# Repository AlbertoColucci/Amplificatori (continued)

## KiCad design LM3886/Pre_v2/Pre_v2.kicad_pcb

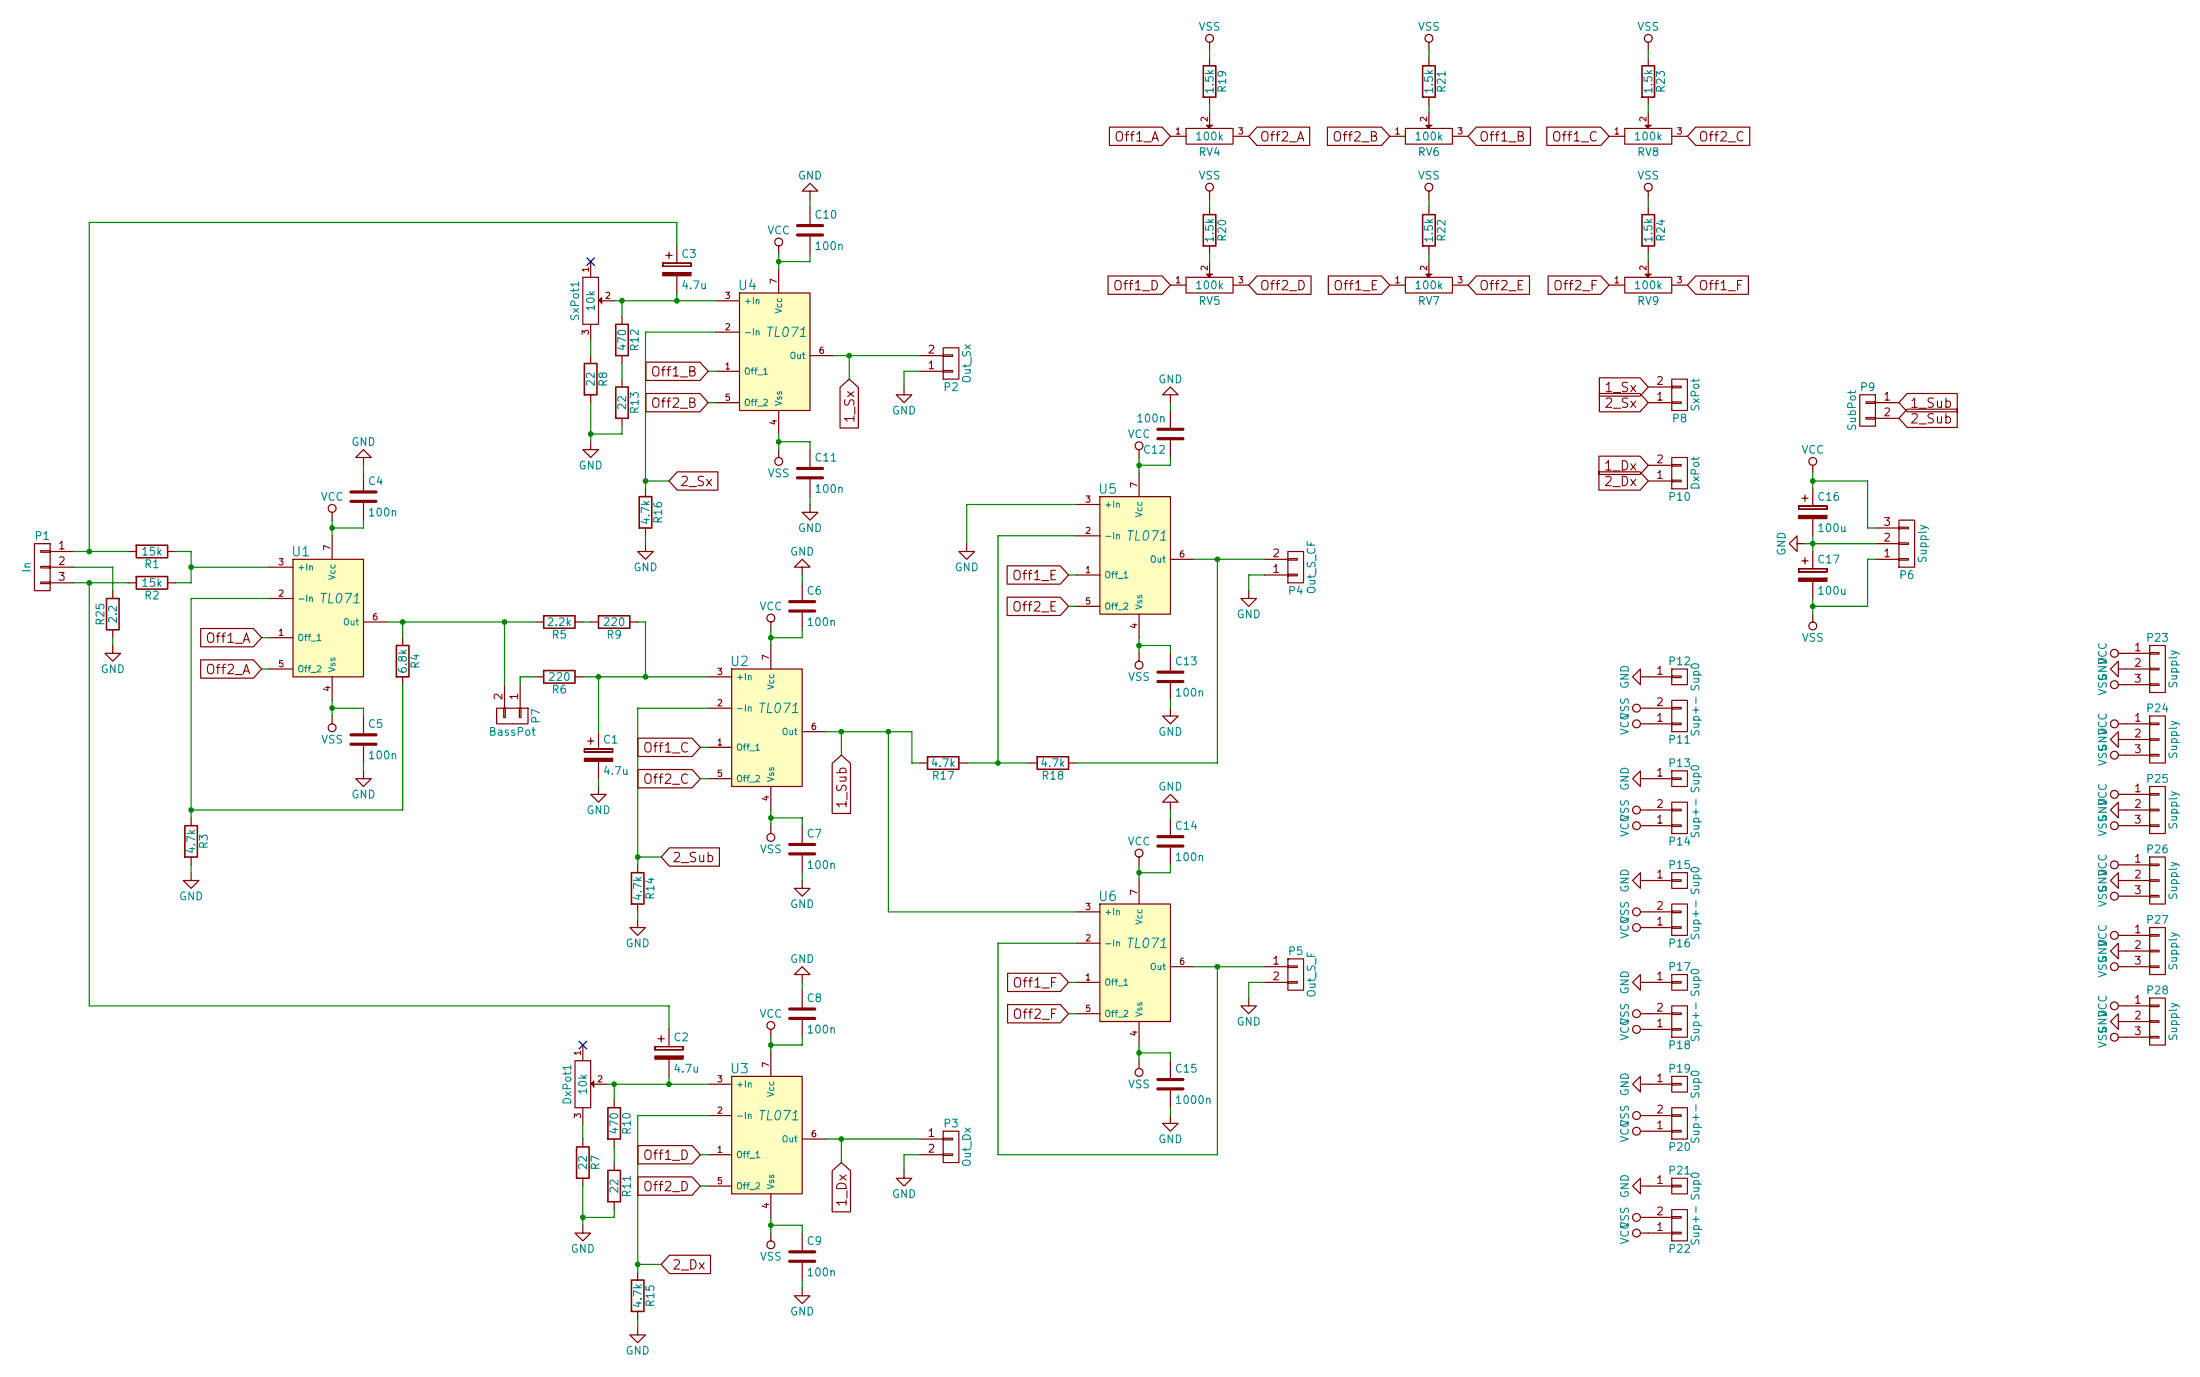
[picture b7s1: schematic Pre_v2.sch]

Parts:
C1, C2, C3: 4.7u; Cap_5x11
C4, C5, C6, C7, C8, C9, C10, C11, C12, C13, C14: 100n; Cap_7x2.5
C15: 1000n; Cap_7x2.5
C16, C17: 100u; Cap_10_5.08
DxPot1: 10k; Potentiometer_Trimmer_Bourns_3296W
P1: In; AK300-3
P2: Out_Sx; AK300-2
P3: Out_Dx; AK300-2
P4: Out_S_CF; AK300-2
P5: Out_S_F; AK300-2
P6: Supply; AK300-3
P7: BassPot; 2-Pin
P8: SxPot; 2-Pin
P9: SubPot; 2-Pin
P10: DxPot; 2-Pin
P11, P14, P16, P18, P20, P22: Sup+-; 2-Pin
P12, P13, P15, P17, P19, P21: Sup0; 1pin
P23, P24, P25, P26, P27, P28: Supply; 3-Pin
R1, R2: 15k; Res_Orizz_10mm
R3, R14, R15, R16, R17, R18: 4.7k; Res_Orizz_10mm
R4: 6.8k; Res_Orizz_10mm
R5: 2.2k; Res_Orizz_10mm
R6, R9: 220; Res_Orizz_10mm
R7, R8, R11, R13: 22; Res_Orizz_10mm
R10, R12: 470; Res_Orizz_10mm
R19, R20, R21, R22, R23, R24: 1.5k; Res_Orizz_10mm
R25: 2.2; Res_Orizz_10mm
RV4, RV5, RV6, RV7, RV8, RV9: 100k; Potentiometer_Trimmer_ACP_CA14v_Horizontal_Px15.0mm_Py10.0mm
SxPot1: 10k; Potentiometer_Trimmer_Bourns_3296W
U1, U2, U3, U4, U5, U6: TL071; DIP-8

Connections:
1_Dx: P3.1, P10.2, U3.6 (Out)
1_Sub: P9.1, R17.2, U2.6 (Out), U6.3 (+In)
1_Sx: P2.2, P8.2, U4.6 (Out)
2_Dx: P10.1, R15.1, U3.2 (-In)
2_Sub: P9.2, R14.1, U2.2 (-In)
2_Sx: P8.1, R16.1, U4.2 (-In)
GND: C1.2, C4.1, C5.2, C6.1, C7.2, C8.1, C9.2, C10.1, C11.2, C12.2, C13.2, C14.1, C15.2, C16.2, C17.1, P2.1, P3.2, P4.1, P5.2, P6.2, P12.1, P13.1, P15.1, P17.1, P19.1, P21.1, P23.2, P24.2, P25.2, P26.2, P27.2, P28.2, R3.2, R7.2, R8.2, R11.2, R13.2, R14.2, R15.2, R16.2, R25.1, U5.3 (+In)
unnamed: C1.1, R6.1, R9.1, U2.3 (+In)
unnamed: C2.1, P1.3, R2.2
unnamed: C2.2, DxPot1.2, R10.1, U3.3 (+In)
unnamed: C3.1, P1.1, R1.2
unnamed: C3.2, R12.1, SxPot1.2, U4.3 (+In)
unnamed: DxPot1.3, R7.1
unnamed: P1.2, R25.2
unnamed: P4.2, R18.1, U5.6 (Out)
unnamed: P5.1, U6.2 (-In), U6.6 (Out)
unnamed: P7.1, R6.2
unnamed: P7.2, R4.1, R5.2, U1.6 (Out)
unnamed: R1.1, R2.1, U1.3 (+In)
unnamed: R3.1, R4.2, U1.2 (-In)
unnamed: R5.1, R9.2
unnamed: R8.1, SxPot1.3
unnamed: R10.2, R11.1
unnamed: R12.2, R13.1
unnamed: R17.1, R18.2, U5.2 (-In)
unnamed: R19.2, RV4.2
unnamed: R20.2, RV5.2
unnamed: R21.2, RV6.2
unnamed: R22.2, RV7.2
unnamed: R23.2, RV8.2
unnamed: R24.2, RV9.2
Off1_A: RV4.1, U1.1 (Off_1)
Off1_B: RV6.3, U4.1 (Off_1)
Off1_C: RV8.1, U2.1 (Off_1)
Off1_D: RV5.1, U3.1 (Off_1)
Off1_E: RV7.1, U5.1 (Off_1)
Off1_F: RV9.3, U6.1 (Off_1)
Off2_A: RV4.3, U1.5 (Off_2)
Off2_B: RV6.1, U4.5 (Off_2)
Off2_C: RV8.3, U2.5 (Off_2)
Off2_D: RV5.3, U3.5 (Off_2)
Off2_E: RV7.3, U5.5 (Off_2)
Off2_F: RV9.1, U6.5 (Off_2)
VCC: C4.2, C6.2, C8.2, C10.2, C12.1, C14.2, C16.1, P6.3, P11.1, P14.1, P16.1, P18.1, P20.1, P22.1, P23.1, P24.1, P25.1, P26.1, P27.1, P28.1, U1.7 (Vcc), U2.7 (Vcc), U3.7 (Vcc), U4.7 (Vcc), U5.7 (Vcc), U6.7 (Vcc)
VSS: C5.1, C7.1, C9.1, C11.1, C13.1, C15.1, C17.2, P6.1, P11.2, P14.2, P16.2, P18.2, P20.2, P22.2, P23.3, P24.3, P25.3, P26.3, P27.3, P28.3, R19.1, R20.1, R21.1, R22.1, R23.1, R24.1, U1.4 (Vss), U2.4 (Vss), U3.4 (Vss), U4.4 (Vss), U5.4 (Vss), U6.4 (Vss)

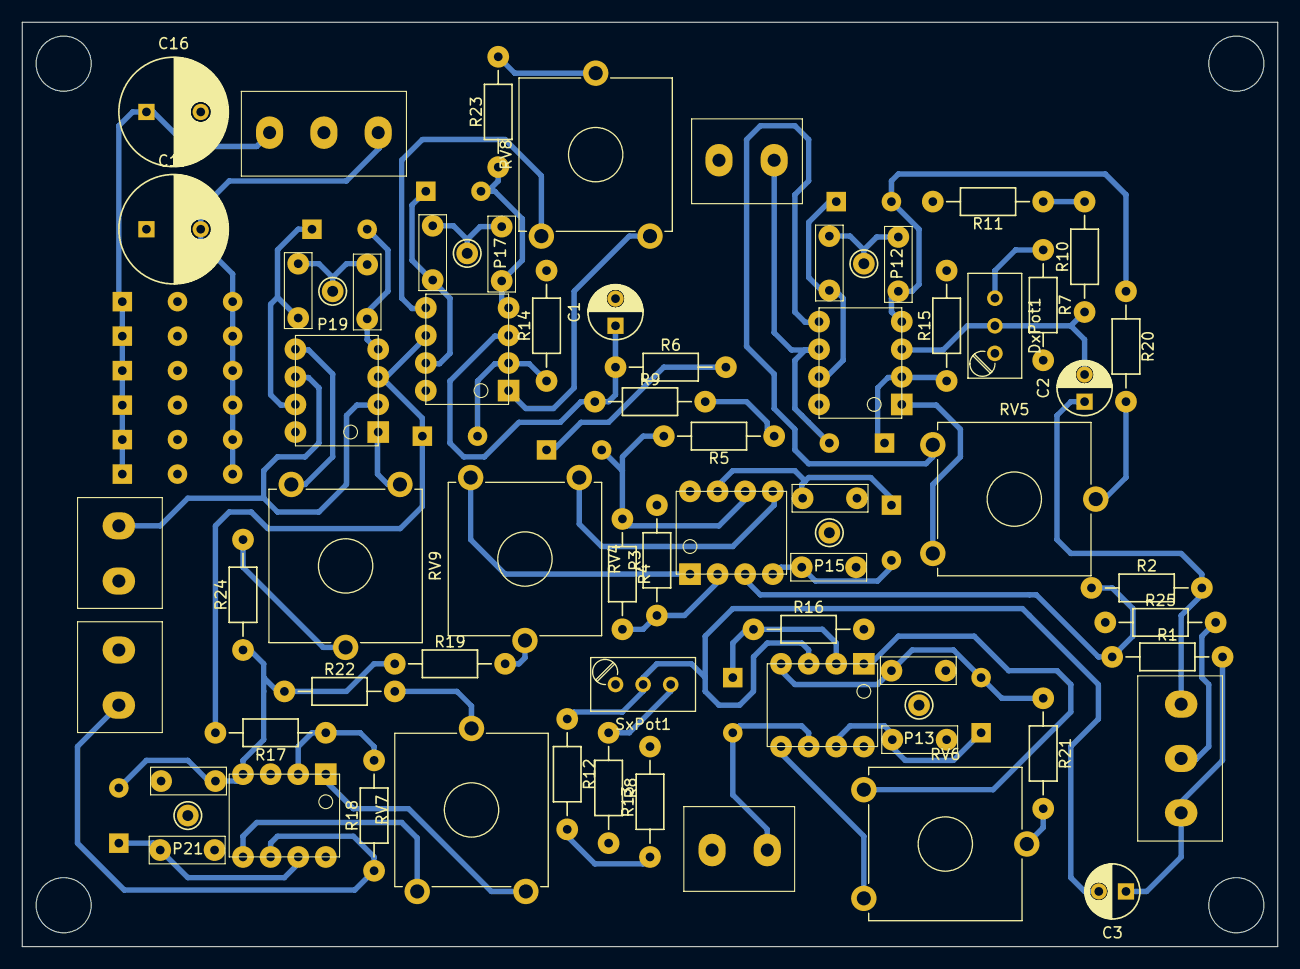
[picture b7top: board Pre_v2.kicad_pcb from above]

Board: 2 copper layers, 115.6 x 85.1 mm, 84 parts (0 on the bottom side), 45 nets.

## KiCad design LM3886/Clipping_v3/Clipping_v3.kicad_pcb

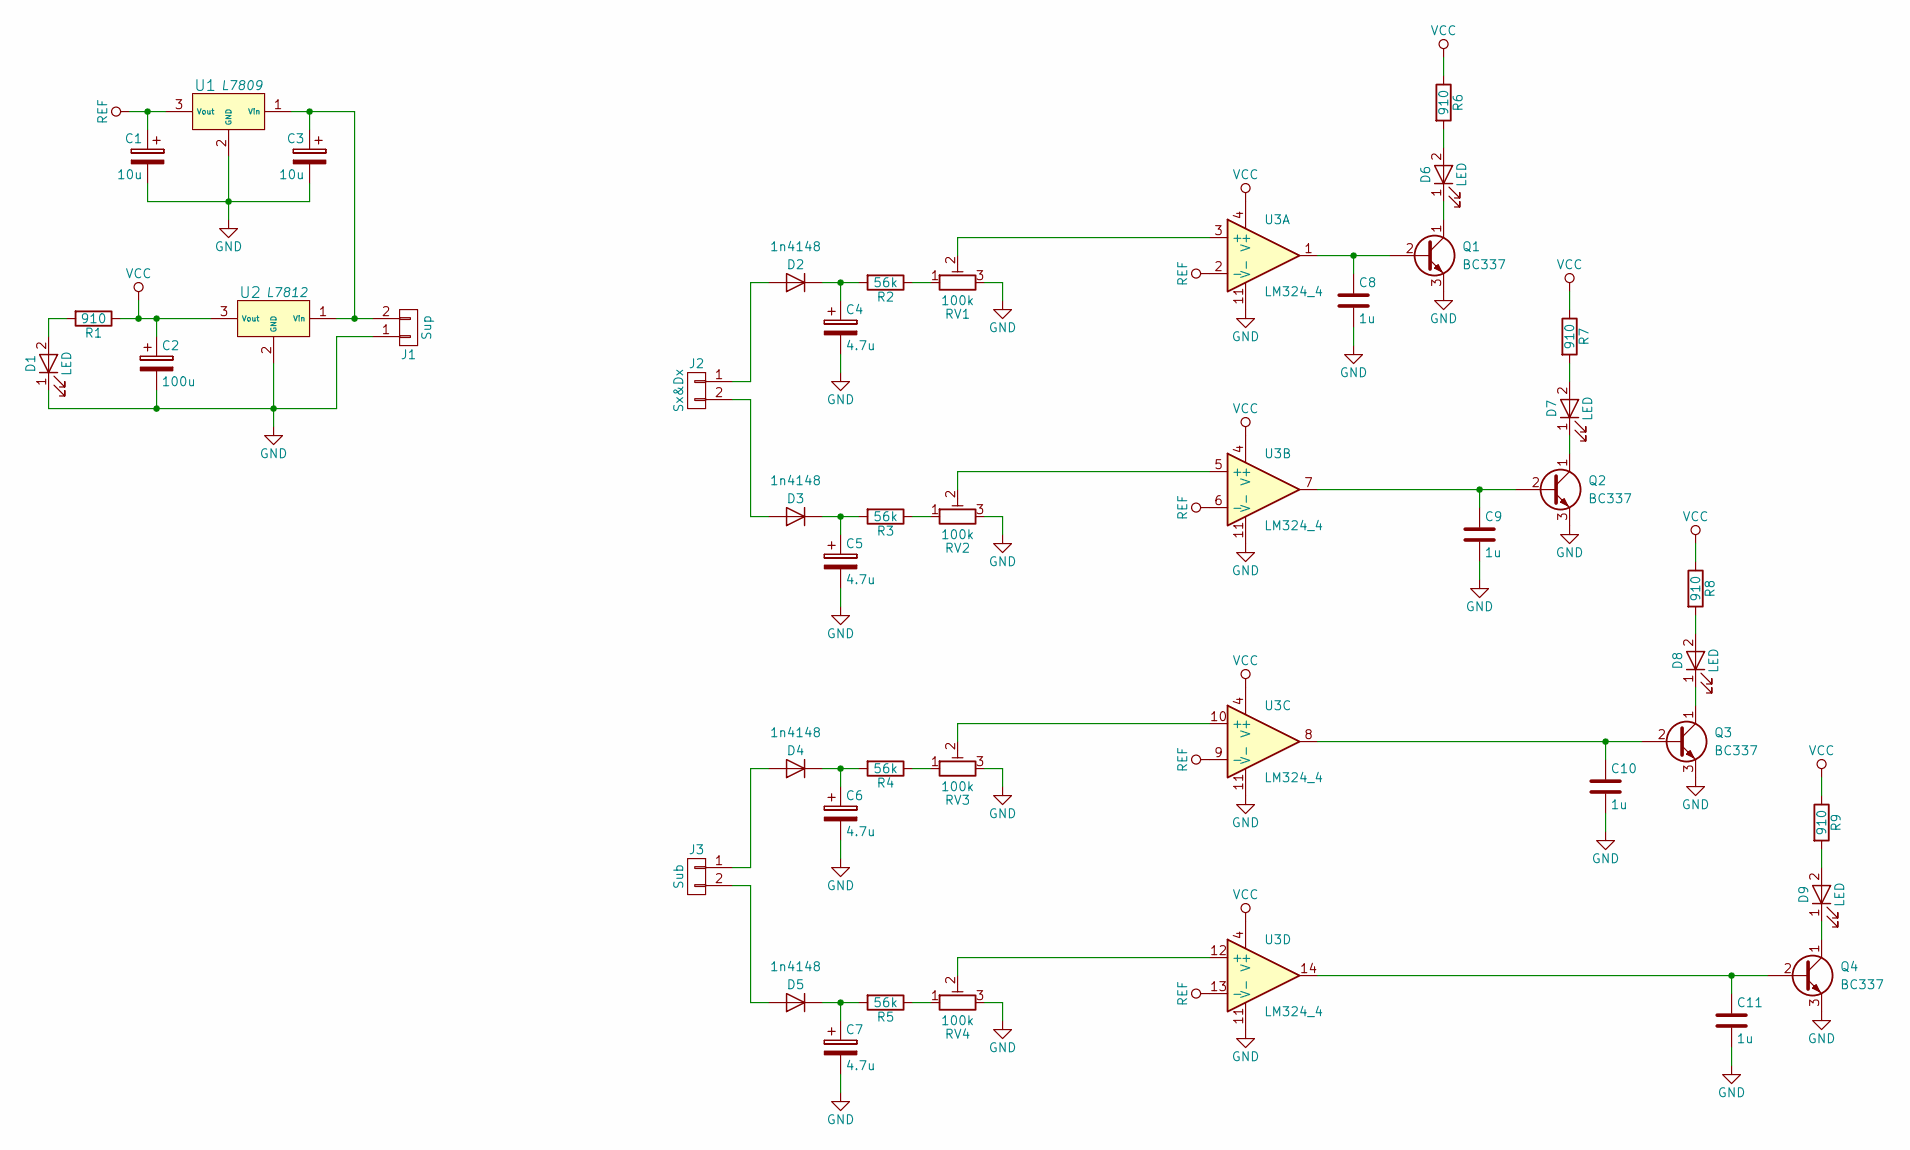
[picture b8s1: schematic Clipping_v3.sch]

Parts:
C1, C3: 10u; Cap_6.3
C2: 100u; Cap_10
C4, C5, C6, C7: 4.7u; Cap_6.3
C8, C9, C10, C11: 1u; Cap_5x2.7
D1, D6, D7, D8, D9: LED; LED_D3.0mm
D2, D3, D4, D5: 1n4148; DO-35
J1: Sup; AK300-2
J2: Sx&Dx; AK300-2
J3: Sub; AK300-2
Q1, Q2, Q3, Q4: BC337; TO-92
R1, R6, R7, R8, R9: 910; Res_Orizz_7mm
R2, R3, R4, R5: 56k; Res_Orizz_7mm
RV1, RV2, RV3, RV4: 100k; Bourns_3006P
U1: L7809; TO-220
U2: L7812; TO-220
U3: LM324_4; DIP-14

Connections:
GND: C1.2, C2.2, C3.2, C4.2, C5.2, C6.2, C7.2, C8.2, C9.2, C10.2, C11.2, D1.1 (K), J1.1, Q1.3 (E), Q2.3 (E), Q3.3 (E), Q4.3 (E), RV1.3, RV2.3, RV3.3, RV4.3, U1.2 (GND), U2.2 (GND), U3.11 (V-)
unnamed: C3.1, J1.2, U1.1 (Vin), U2.1 (Vin)
unnamed: C4.1, D2.1 (K), R2.2
unnamed: C5.1, D3.1 (K), R3.2
unnamed: C6.1, D4.1 (K), R4.2
unnamed: C7.1, D5.1 (K), R5.2
unnamed: C8.1, Q1.2 (B), U3.1
unnamed: C9.1, Q2.2 (B), U3.7
unnamed: C10.1, Q3.2 (B), U3.8
unnamed: C11.1, Q4.2 (B), U3.14
unnamed: D1.2 (A), R1.2
unnamed: D2.2 (A), J2.1
unnamed: D3.2 (A), J2.2
unnamed: D4.2 (A), J3.1
unnamed: D5.2 (A), J3.2
unnamed: D6.1 (K), Q1.1 (C)
unnamed: D6.2 (A), R6.2
unnamed: D7.1 (K), Q2.1 (C)
unnamed: D7.2 (A), R7.2
unnamed: D8.1 (K), Q3.1 (C)
unnamed: D8.2 (A), R8.2
unnamed: D9.1 (K), Q4.1 (C)
unnamed: D9.2 (A), R9.2
unnamed: R2.1, RV1.1
unnamed: R3.1, RV2.1
unnamed: R4.1, RV3.1
unnamed: R5.1, RV4.1
unnamed: RV1.2, U3.3 (+)
unnamed: RV2.2, U3.5 (+)
unnamed: RV3.2, U3.10 (+)
unnamed: RV4.2, U3.12 (+)
REF: C1.1, U1.3 (Vout), U3.2 (-), U3.6 (-), U3.9 (-), U3.13 (-)
VCC: C2.1, R1.1, R6.1, R7.1, R8.1, R9.1, U2.3 (Vout), U3.4 (V+)

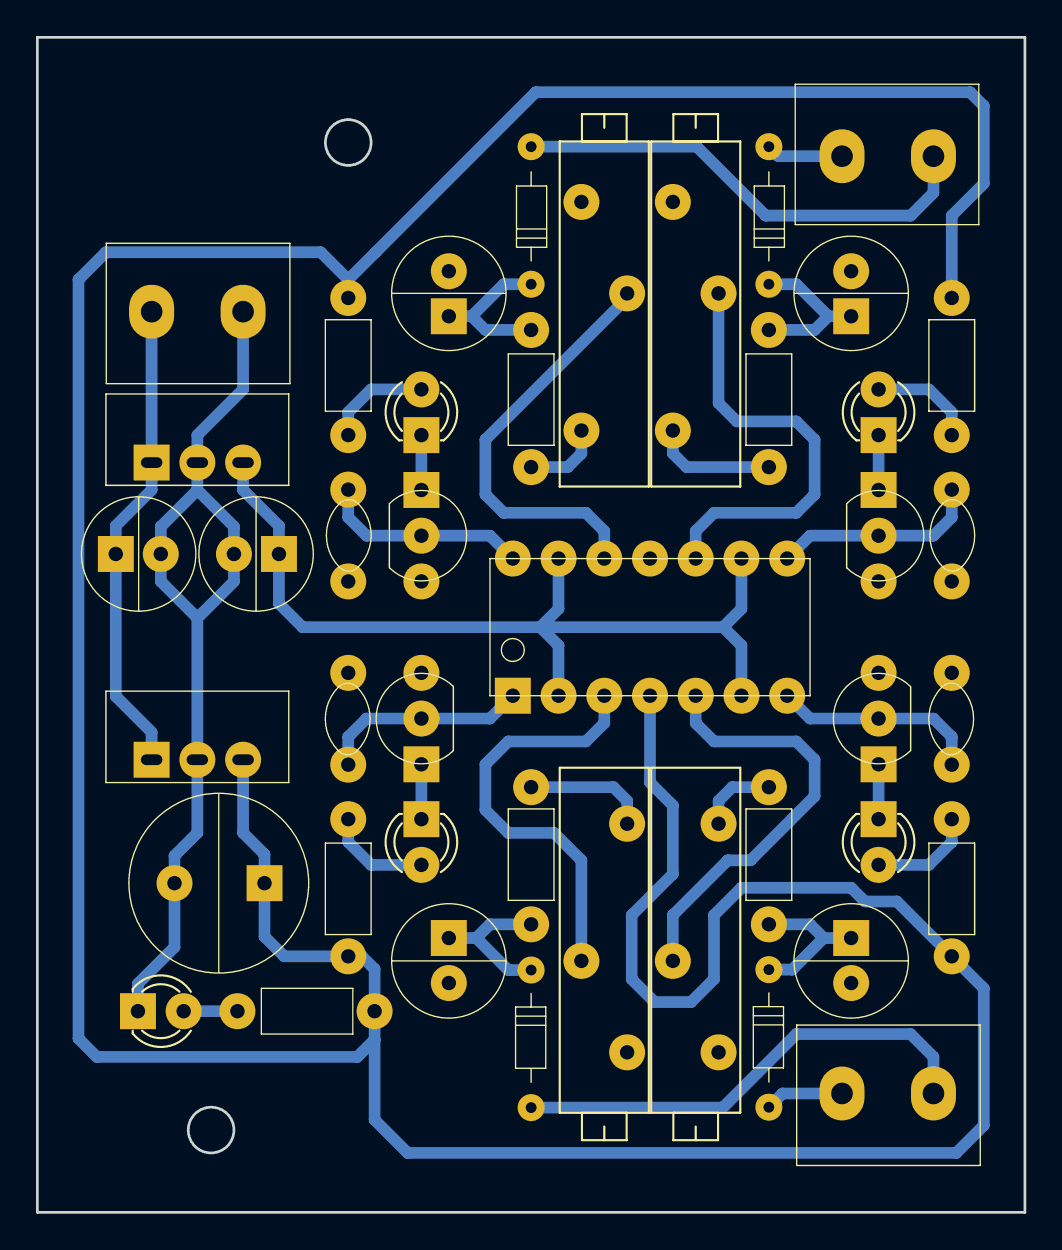
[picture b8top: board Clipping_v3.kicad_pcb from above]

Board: 2 copper layers, 54.9 x 65.3 mm, 43 parts (0 on the bottom side), 33 nets.
